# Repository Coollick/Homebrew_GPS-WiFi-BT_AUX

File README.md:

# Homebrew_GPS-WiFi-BT_AUX

# Pinout for PCB v2.0

Added 4K7 pullup resistors on SDA and SCL

### Pin change compared to V1

- D4 (ESP Wifi Off) changed to D36
- D5 (ESP Wifi Mode) changed to D39
- D18 (ESP Restore Defaults) changed to D34
- GPS_RX changed to D33
- GPS_TX changed to D25
- I2C pins
    - SDA (D21)
    - SCL (D22)
- SPI pins:
    - CS (D5)
    - CLK (D18)
    - MISO (D19)
    - MOSI (D23)
    - RST (D13)

# Shared project on OshPark (PCB v2.0)
https://oshpark.com/shared_projects/jyQbF7Wx

When soldering the PCB, make sure you adjust the voltage of the DC step down after soldering both diode, to make sure that the output after the diode is 5V.

## 3D Printing box design
https://www.thingiverse.com/thing:4806408

https://www.tinkercad.com/things/dk77gXFjQE0-homebrewgps-wifi-btaux

## Hardware list
- Amphenol RJ12 socket 54601-906WPLF
- ESP-32 30Pin development board
- Beitian BN-180 GPS
- 1x 74HC125 (Sometimes called 74HC125N)
- 2x 50kΩ resistor (or 51kΩ)
- 3x 330Ω resistor
- 2x 4,7KΩ (4700Ω) resistor
- 2 diode (any will do, something like 1N5819 or 1N5822)
- 1 DC sep down module (with pin OUT, GND and IN on the same side, in that order - Often marked +VO, GND and IN+)
- Optional: 1x SSD1306 I2C OLED screen (128x64 0.96 inch)

You can find an aliexpress wishlist with the hardware list [here](https://s.click.aliexpress.com/e/_DBdeQVt) (only the RJ12 socket cannot be ordered from Aliexpress)

## Arduino code
An example source code is available here : [Homebrew_GPS-WiFi-BT_AUX.ino](Homebrew_GPS-WiFi-BT_AUX/Homebrew_GPS-WiFi-BT_AUX.ino) 
You can configure certain part by changing the following parameter

| Parameter  | Function |
| ------------- | ------------- |
| VERBOSE  | Display debug information on serial port, turn off after test  |
| BT_ENABLED  | When false, Bluetooth code is completely left out  |
| ETH_ENABLED  | Always false for this project, only set to true if you want to add ethernet  |
| FORCE_WIFI_ON  | When true, wifi is always on and wifi switch is ignored  |
| FORCE_AP_MODE  | When true, Access Point mode is always on, this allow to connect directly to homebrew via wifi  |
| USE_OLED  | When false, OLED code is completely left out  |

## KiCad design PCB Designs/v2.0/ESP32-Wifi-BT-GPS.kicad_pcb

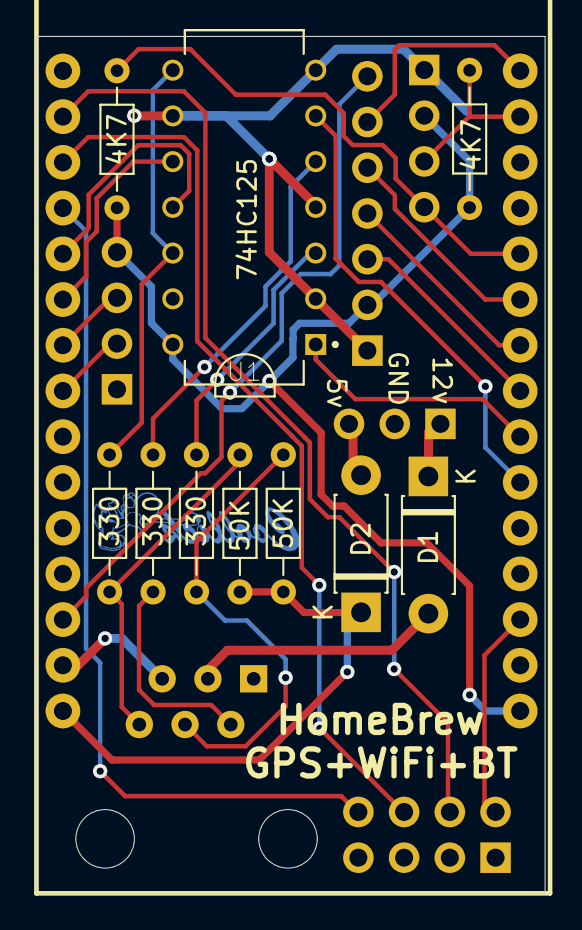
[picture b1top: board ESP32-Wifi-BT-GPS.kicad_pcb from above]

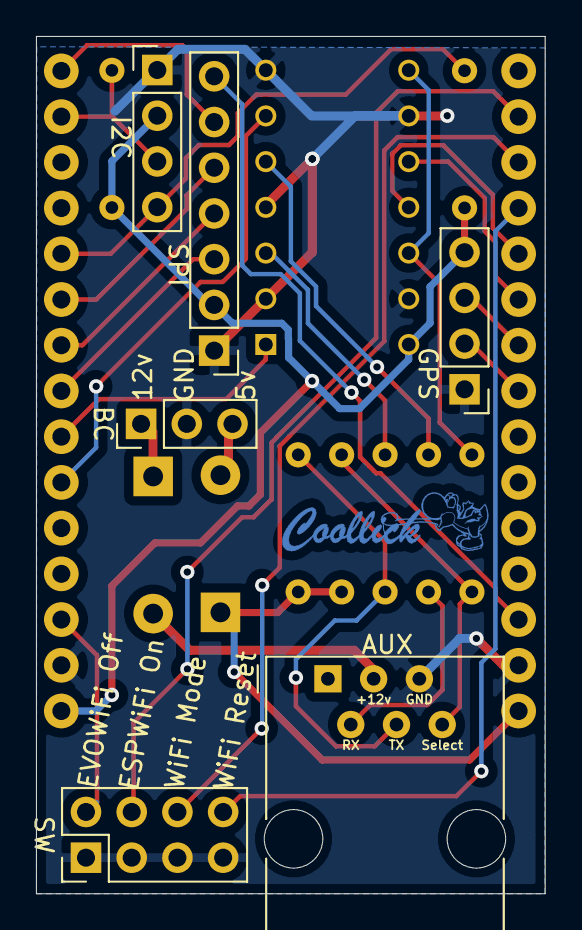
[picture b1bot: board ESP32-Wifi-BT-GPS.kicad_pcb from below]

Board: 2 copper layers, 28.3 x 47.6 mm, 18 parts (7 on the bottom side), 29 nets.

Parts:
4K7, 4K7#2: 4K7; R_Axial_DIN0204_L3.6mm_D1.6mm_P7.62mm_Horizontal
50K, 50K#2: 50K; R_Axial_DIN0204_L3.6mm_D1.6mm_P7.62mm_Horizontal
330, 330#2, 330#3: 330R; R_Axial_DIN0204_L3.6mm_D1.6mm_P7.62mm_Horizontal
AUX: RJ12-AUX; RJ12_Amphenol_54601
BC: BUCK; PinHeader_1x03_P2.54mm_Vertical
D1, D2: D; D_DO-41_SOD81_P7.62mm_Horizontal
GPS: GPS; PinHeader_1x04_P2.54mm_Vertical
I2C: I2C; PinHeader_1x04_P2.54mm_Vertical
SPI: SPI; PinHeader_1x07_P2.54mm_Vertical
SW: Conn_02x04_Odd_Even; PinHeader_2x04_P2.54mm_Vertical
U1: SN74HC125N; DIP794W45P254L1969H508Q14
U2: ESP32DEVKITV1; ESP32-DEVKITV1
svg2mod: G***; Coollick

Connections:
3OE: U1.10, U2.D32
4Y: U1.11, U2.D35
+3V3: 4K7.2, 4K7#2.1, GPS.4, I2C.2, SPI.2, U1.14, U2.3V3
+5V: 50K.2, 50K#2.2, D2.1, U2.VIN
+12V: AUX.3, D1.2
CLK: SPI.4, U2.D18
CS: SPI.3, U2.D5
ESP-Restore-Defaults: SW.8, U2.D34
ESP-Wifi-Mode: SW.6, U2.D39
ESP-Wifi-Off: SW.4, U2.D36
EVO-Wifi-Off: SW.2, U2.D15
GND: AUX.5, BC.2, GPS.1, I2C.1, SPI.1, SW.1, SW.3, SW.5, SW.7, U1.2, U1.4, U1.7, U1.9, U1.13, U2.GND@1, U2.GND@2
GPS_RX: GPS.3, U2.D33
GPS_TX: GPS.2, U2.D25
MISO: SPI.5, U2.D19
MOSI: SPI.6, U2.D23
unnamed: BC.1, D1.1
unnamed: BC.3, D2.2
unnamed: 330#2.2, AUX.2
unnamed: 50K.1, 330#3.2, AUX.4
unnamed: 50K#2.1, 330.2, AUX.6
unnamed: 330#2.1, U1.5
unnamed: 330.1, U1.8, U1.12
unnamed: 330#3.1, U1.3
RST: SPI.7, U2.D13
RX2: U1.6, U2.D16
SCL: 4K7#2.2, I2C.3, U2.D22
SDA: 4K7.1, I2C.4, U2.D21
TX2: U1.1, U2.D17

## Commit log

2021-03-26 Added PCB v1.0-compact
2021-03-26 add images
2021-03-28 pcb v1.0 fix reversed silkscreen 5v-12v
2021-03-28 add v2.0 pcb (remapped pins)
2022-09-18 Added example code based on Mark Lord's code
2022-10-01 Update README.md - Added hardware list + Link to PCB
2022-10-01 Update README.md - Added OLED screen in hardware list
2022-10-02 Added OLED support - Added LED support
2022-10-02 Update README.md
    Added DC step down to hardware list + setup hint
    Added link to the arduino code
    Added description of the parameter in code
2022-10-02 Update README.md - Added ESP32 to the hardware list
2023-09-27 Add files via upload
    added image of v1 schematic
